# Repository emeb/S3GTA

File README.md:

# S3GTA
A Eurorack effects module based on the ESP32S3

## Abstract
This project builds on my previous ESP32S2 design:

https://github.com/emeb/ESP32S2_Audio

taking it further with a circular LCD, touch sensing and more CV inputs. It's
based on an ESP32S3 with 4MB flash and 2MB PSRAM in the package, as well as
dual CPU cores to potentially provide more DSP bandwidth.

### What's with the name?
I'm terrible at coming up with catchy names for my projects and this one is no
departure from that. It breaks down thus:
* S3 from the ESP32S3 processor
* G from the GC9A01 LCD
* T from the circular touch sensor
* A from audio I/O

## Hardware
The hardware consists of two PCBs - a front-panel board that provides the main
Eurorack user interface including a 240x240 circular LCD with a circular touch
sensor surrounding it and the MCU & audio codec, coupled with a back board that
includes the Eurorack power as well as audio and CV interfaces for the front-panel.

The front-panel PCB contains the following components:
* ESP32-S3FH4R2 MCU with 4MB flash and 2MB PSRAM integrated in the package
* WM8731 I2S audio codec
* 4 pad proportional circular touch sensor
* 4 CVs, stereo in/out and sync + button interfaces to back board.
* optional USB and Qwicc connectors

The back board has
* Standard Eurorack 16-pin shrouded power connector
* Four +/-5V CV inputs and associated analog signal conditioning
* Four offset pots for the CVs
* Two +/-7V Audio inputs and associated analog signal conditioning 
* Two +/-7V Audio outputs and associated analog drivers
* Tap tempo button
* Sync input jack

## Firmware
A demonstration firmware is included that exercises all of the capabilities of
the system, including the LCD, UI button, CV inputs and stereo audio I/O. It is
a basic multi-effects unit that supports a complement of audio DSP algorithms
that are easily extended by adding standardized modules to a data structure.
As provided here just three algorithms are available:
* Simple pass-thru with no processing
* Simple gain control
* Lowpass, Highpass and Bandpass filters
* Basic "clean delay" with crossfaded deglitching during delay changes.

Other algorithms have been tested including phasers, flangers, frequency shifters,
resampling delays and reverbs, but these are not publicly released at this time.

## Findings
The ESP32Ss is not bad for doing audio and the I2S driver in ESP-IDF V5.2.3 does
include good support for realtime audio processing. There are a few hiccups in
the way it works that are commented in the source code, but overall it does a
good job of supporting audio effects processing.

I found that in general the DSP on the ESP32S3 was usable, although not as
efficient as on ARM processors. Some algorithms showed significantly higher CPU
loading on the ESP32S3 than on ARM Cortex M7, even accounting for clock speed
differences. Studying the disassembly of the object code suggests that the full
DSP capability of the ESP32S3 Xtensa CPU ISA isn't being brought to bear by the
GCC compiler - for example the available multiply-accumulate instructions were
not used in cases where they may have reduced overall instruction counts.

## Future work
The UI is fairly primitive and doesn't make effective use of the circular touch
sensor. In the initial release there are only two "soft buttons" that employ
the touch sensor to select the current algorithm and this could be extended
to allow more soft buttons, deeper menuing and even continuously variable
adjustmets for things like on-board modulation.

The graphic elements on the circular LCD are also pretty tiny and hard to read
while also not taking full advantage of the available LCD area. It would be
interesting to "lean in" to the round nature of the display with more arcs
and circular UI elements. Fatter lines and larger fonts would help a lot too.
One option is to ditch the home-made graphics library I used here and try to
leverage LVGL which is available as an external module in ESP IDF - I did a
bit of research into this at the outset but went with my existing graphics
for ease of porting older code.

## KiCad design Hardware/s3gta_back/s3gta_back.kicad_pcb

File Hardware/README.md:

# S3GTA Hardware
This directory contains the Kicad designs for the front and back PCBs

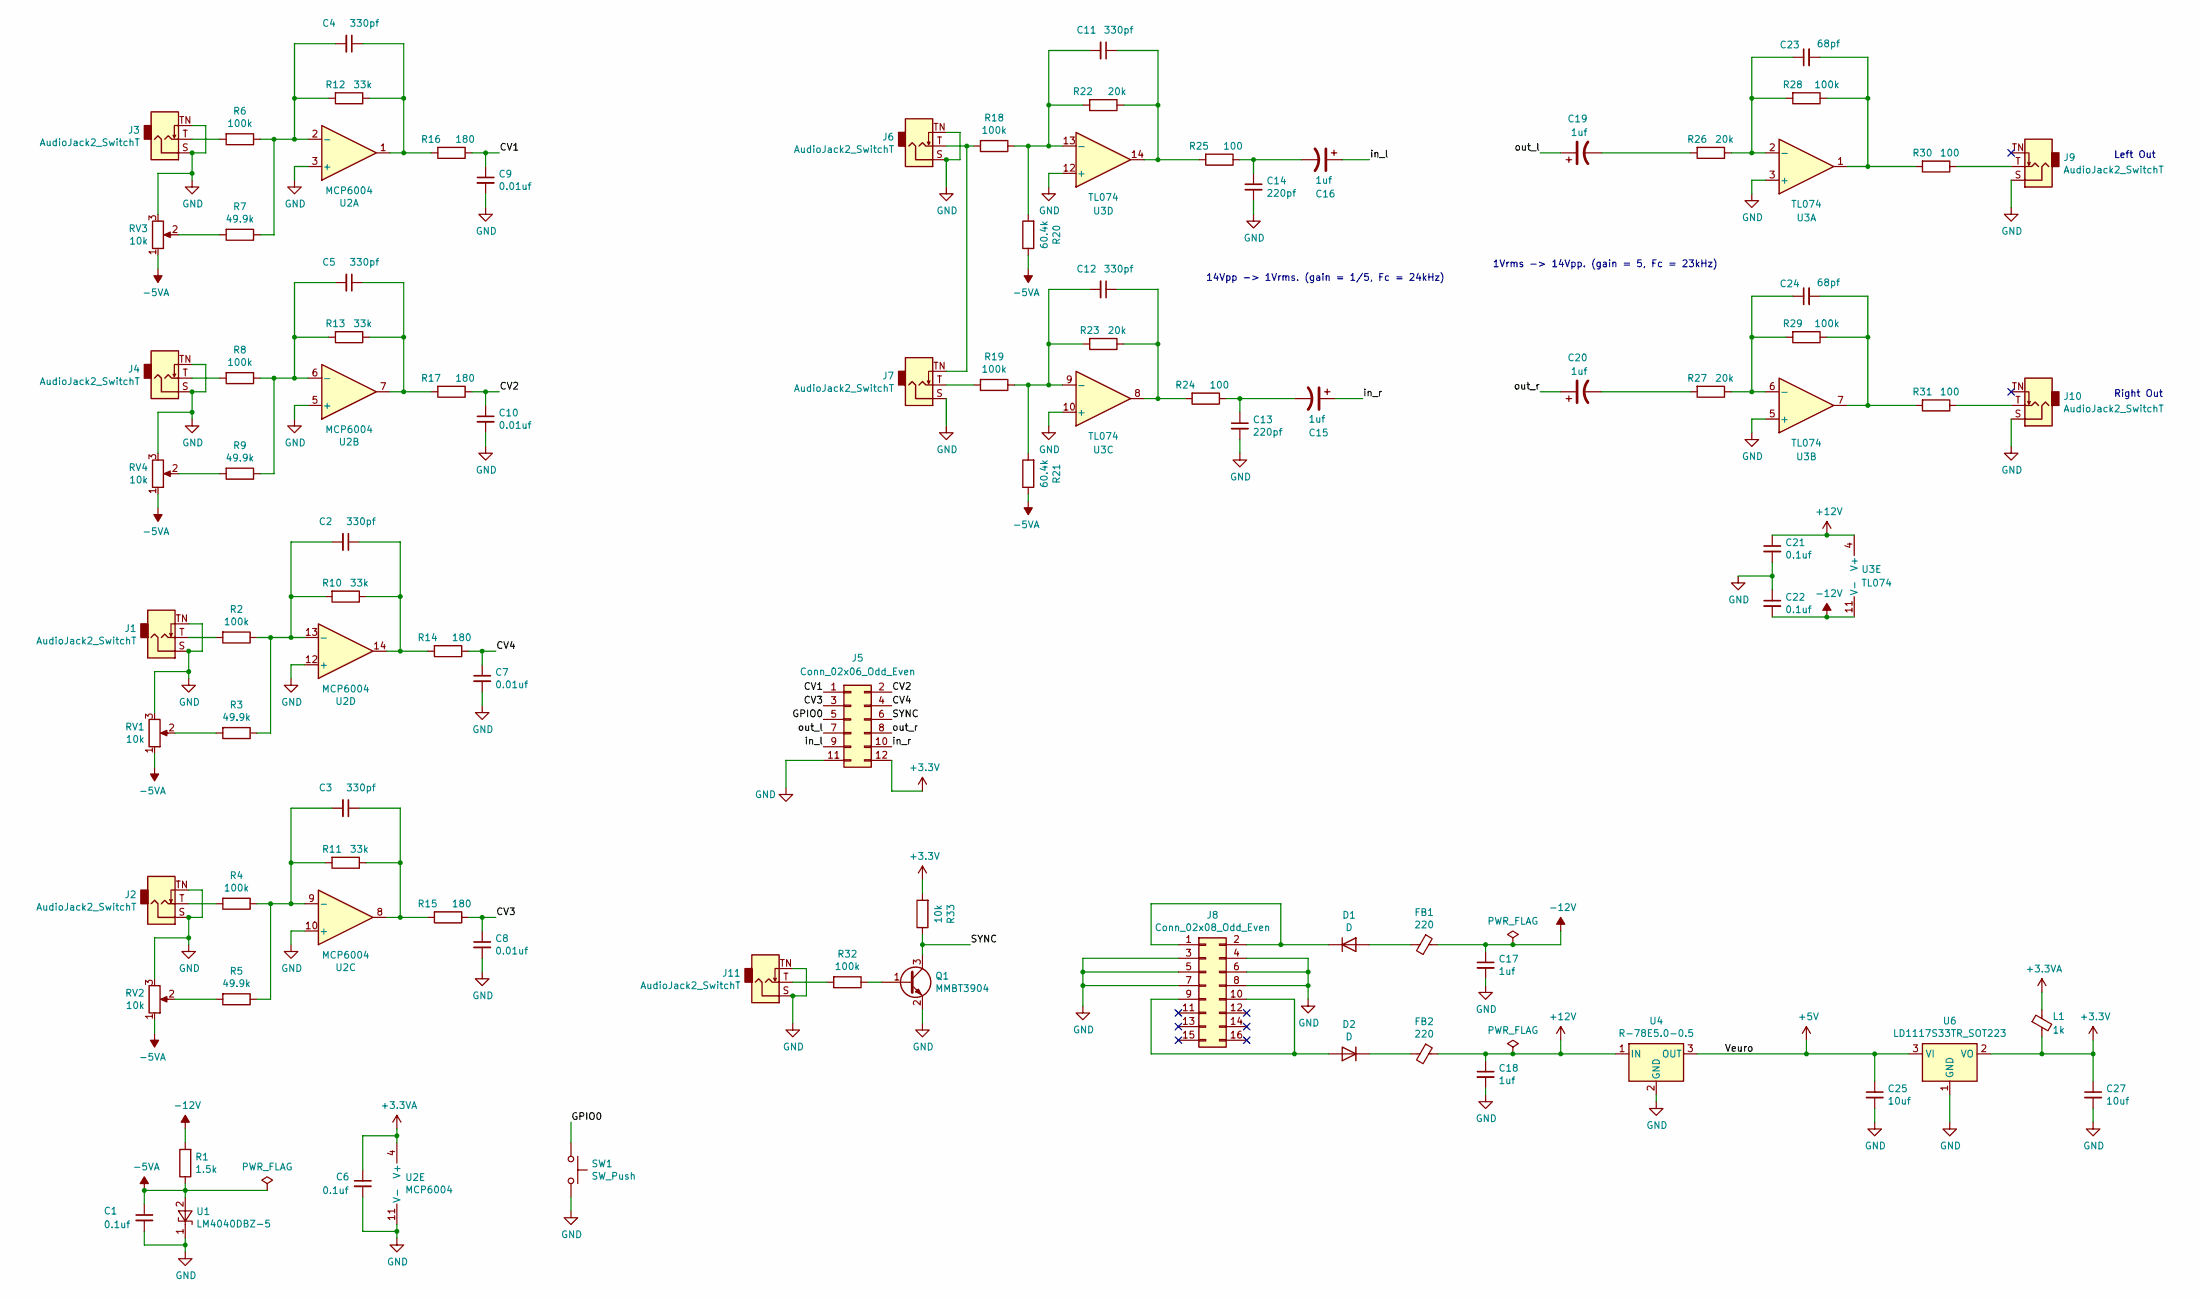
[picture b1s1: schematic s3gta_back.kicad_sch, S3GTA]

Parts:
C1, C6, C21, C22: 0.1uf; C_0603_1608Metric
C2, C3, C4, C5, C11, C12: 330pf; C_0603_1608Metric
C7, C8, C9, C10: 0.01uf; C_0603_1608Metric
C13, C14: 220pf; C_0603_1608Metric
C15, C16, C19, C20: 1uf; CP_Elec_4x5.3
C17, C18: 1uf; C_0603_1608Metric
C23, C24: 68pf; C_0603_1608Metric
C25, C27: 10uf; C_0805_2012Metric
D1, D2: D; D_SMA
FB1, FB2: 220; L_0805_2012Metric
J1, J2, J3, J4, J6, J7, J9, J10, J11: AudioJack2_SwitchT; Jack_3.5mm_QingPu_WQP-PJ398SM_Vertical_CircularHoles
J5: Conn_02x06_Odd_Even; PinSocket_2x06_P2.54mm_Vertical
J8: Conn_02x08_Odd_Even; con16_2X8_S4_TEC
L1: 1k; L_0603_1608Metric
Q1: MMBT3904; SOT-23
R1: 1.5k; R_0603_1608Metric
R2, R4, R6, R8, R18, R19, R28, R29, R32: 100k; R_0603_1608Metric
R3, R5, R7, R9: 49.9k; R_0603_1608Metric
R10, R11, R12, R13: 33k; R_0603_1608Metric
R14, R15, R16, R17: 180; R_0603_1608Metric
R20, R21: 60.4k; R_0603_1608Metric
R22, R23, R26, R27: 20k; R_0603_1608Metric
R24, R25, R30, R31: 100; R_0603_1608Metric
R33: 10k; R_0603_1608Metric
RV1, RV2, RV3, RV4: 10k; R0904N
SW1: SW_Push; SW_PUSH_6mm
U1: LM4040DBZ-5; SOT-23
U2: MCP6004; SOIC-14_3.9x8.7mm_P1.27mm
U3: TL074; SOIC-14_3.9x8.7mm_P1.27mm
U4: R-78E5.0-0.5; Converter_DCDC_RECOM_R-78E-0.5_THT
U6: LD1117S33TR_SOT223; SOT-223-3_TabPin2

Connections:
+3.3V: C27.1, J5.12, L1.2, R33.2, U6.2 (VO)
+3.3VA: C6.1, L1.1, U2.4 (V+)
+5V: C25.1, U4.3 (OUT), U6.3 (VI)
+12V: C18.1, C21.1, FB2.1, U3.4 (V+), U4.1 (IN)
-5VA: C1.1, R1.1, R20.1, R21.1, RV1.1, RV2.1, RV3.1, RV4.1, U1.2 (A)
-12V: C17.1, C22.2, FB1.1, R1.2, U3.11 (V-)
/CV1: C9.1, J5.1, R16.1
/CV2: C10.1, J5.2, R17.1
/CV3: C8.1, J5.3, R15.1
/CV4: C7.1, J5.4, R14.1
/GPIO0: J5.5, SW1.1
/SYNC: J5.6, Q1.3 (C), R33.1
/in_l: C16.1, J5.9
/in_r: C15.1, J5.10
/out_l: C19.1, J5.7
/out_r: C20.1, J5.8
GND: C1.2, C6.2, C7.2, C8.2, C9.2, C10.2, C13.2, C14.2, C17.2, C18.2, C21.2, C22.1, C25.2, C27.2, J1.S, J1.TN, J2.S, J2.TN, J3.S, J3.TN, J4.S, J4.TN, J5.11, J6.S, J6.TN, J7.S, J8.3, J8.4, J8.5, J8.6, J8.7, J8.8, J9.S, J10.S, J11.S, J11.TN, Q1.2 (E), RV1.3, RV2.3, RV3.3, RV4.3, SW1.2, U1.1 (K), U2.3 (+), U2.5 (+), U2.10 (+), U2.11 (V-), U2.12 (+), U3.3 (+), U3.5 (+), U3.10 (+), U3.12 (+), U4.2 (GND), U6.1 (GND)
unnamed: C2.1, R10.1, R14.2, U2.14
unnamed: C3.1, R11.1, R15.2, U2.8
unnamed: C4.1, R12.1, R16.2, U2.1
unnamed: C5.1, R13.1, R17.2, U2.7
unnamed: C11.1, R22.1, R25.2, U3.14
unnamed: C12.1, R23.1, R24.2, U3.8
unnamed: C13.1, C15.2, R24.1
unnamed: C14.1, C16.2, R25.1
unnamed: C19.2, R26.2
unnamed: C20.2, R27.2
unnamed: C23.2, R28.1, R30.2, U3.1
unnamed: C24.2, R29.1, R31.2, U3.7
unnamed: D1.2 (A), FB1.2
unnamed: D1.1 (K), J8.1, J8.2
unnamed: D2.2 (A), J8.9, J8.10
unnamed: D2.1 (K), FB2.2
unnamed: J1.T, R2.2
unnamed: J2.T, R4.2
unnamed: J3.T, R6.2
unnamed: J4.T, R8.2
unnamed: J6.T, J7.TN, R18.2
unnamed: J7.T, R19.2
unnamed: J9.T, R30.1
unnamed: J10.T, R31.1
unnamed: J11.T, R32.2
unnamed: Q1.1 (B), R32.1
unnamed: R3.2, RV1.2
unnamed: R5.2, RV2.2
unnamed: R7.2, RV3.2
unnamed: R9.2, RV4.2
unnamed: C4.2, R6.1, R7.1, R12.2, U2.2 (-)
unnamed: C5.2, R8.1, R9.1, R13.2, U2.6 (-)
unnamed: C3.2, R4.1, R5.1, R11.2, U2.9 (-)
unnamed: C2.2, R2.1, R3.1, R10.2, U2.13 (-)
unnamed: C23.1, R26.1, R28.2, U3.2 (-)
unnamed: C24.1, R27.1, R29.2, U3.6 (-)
unnamed: C12.2, R19.1, R21.2, R23.2, U3.9 (-)
unnamed: C11.2, R18.1, R20.2, R22.2, U3.13 (-)

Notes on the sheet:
1Vrms -> 14Vpp. (gain = 5, Fc = 23kHz)
14Vpp -> 1Vrms. (gain = 1/5, Fc = 24kHz)
Right Out
Left Out

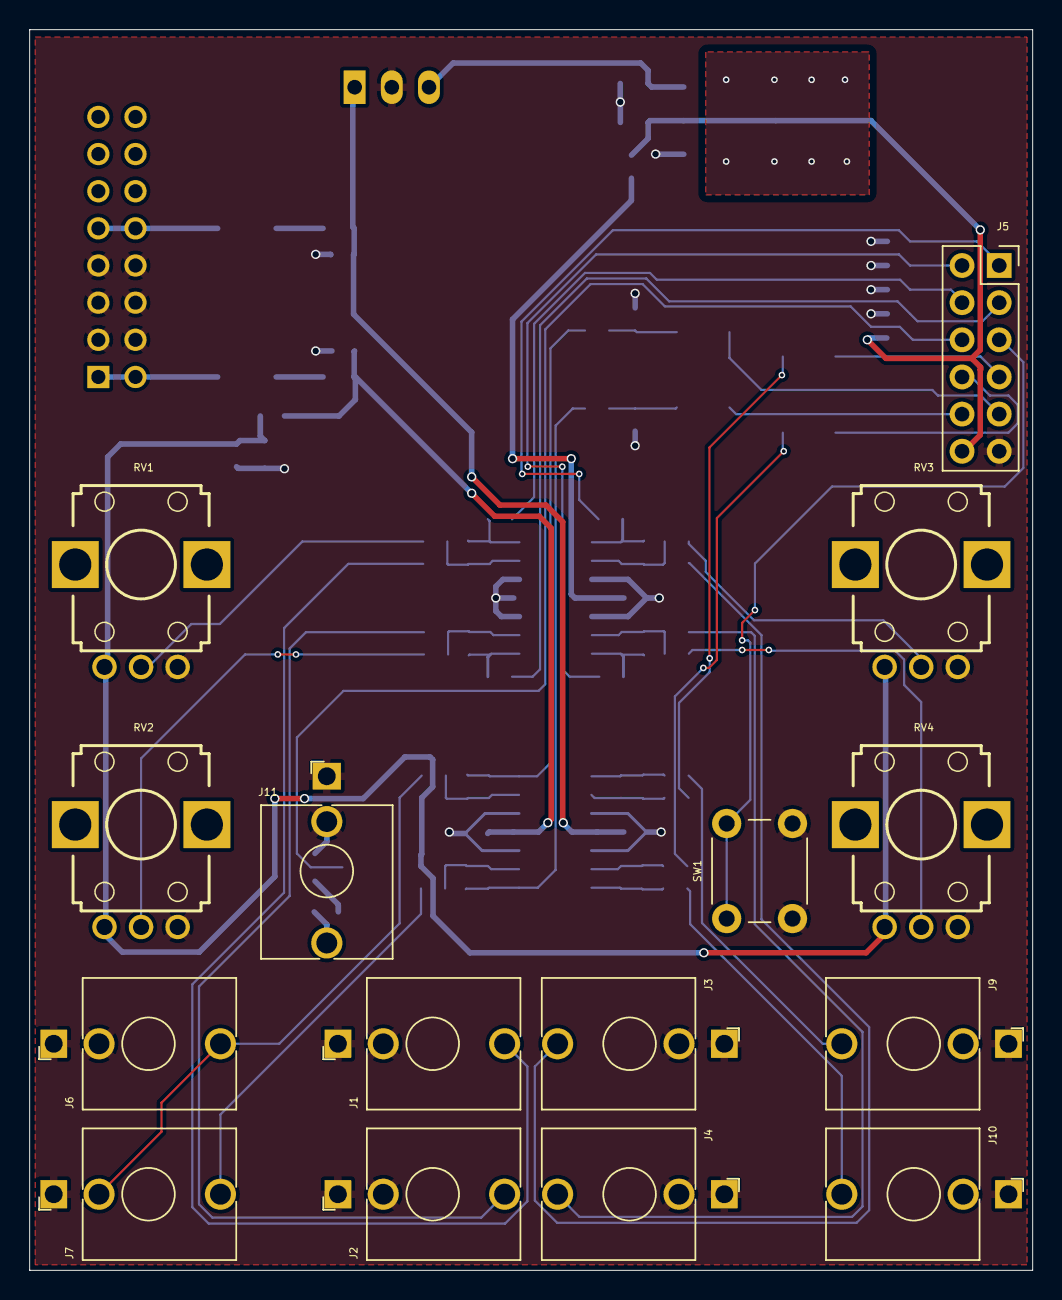
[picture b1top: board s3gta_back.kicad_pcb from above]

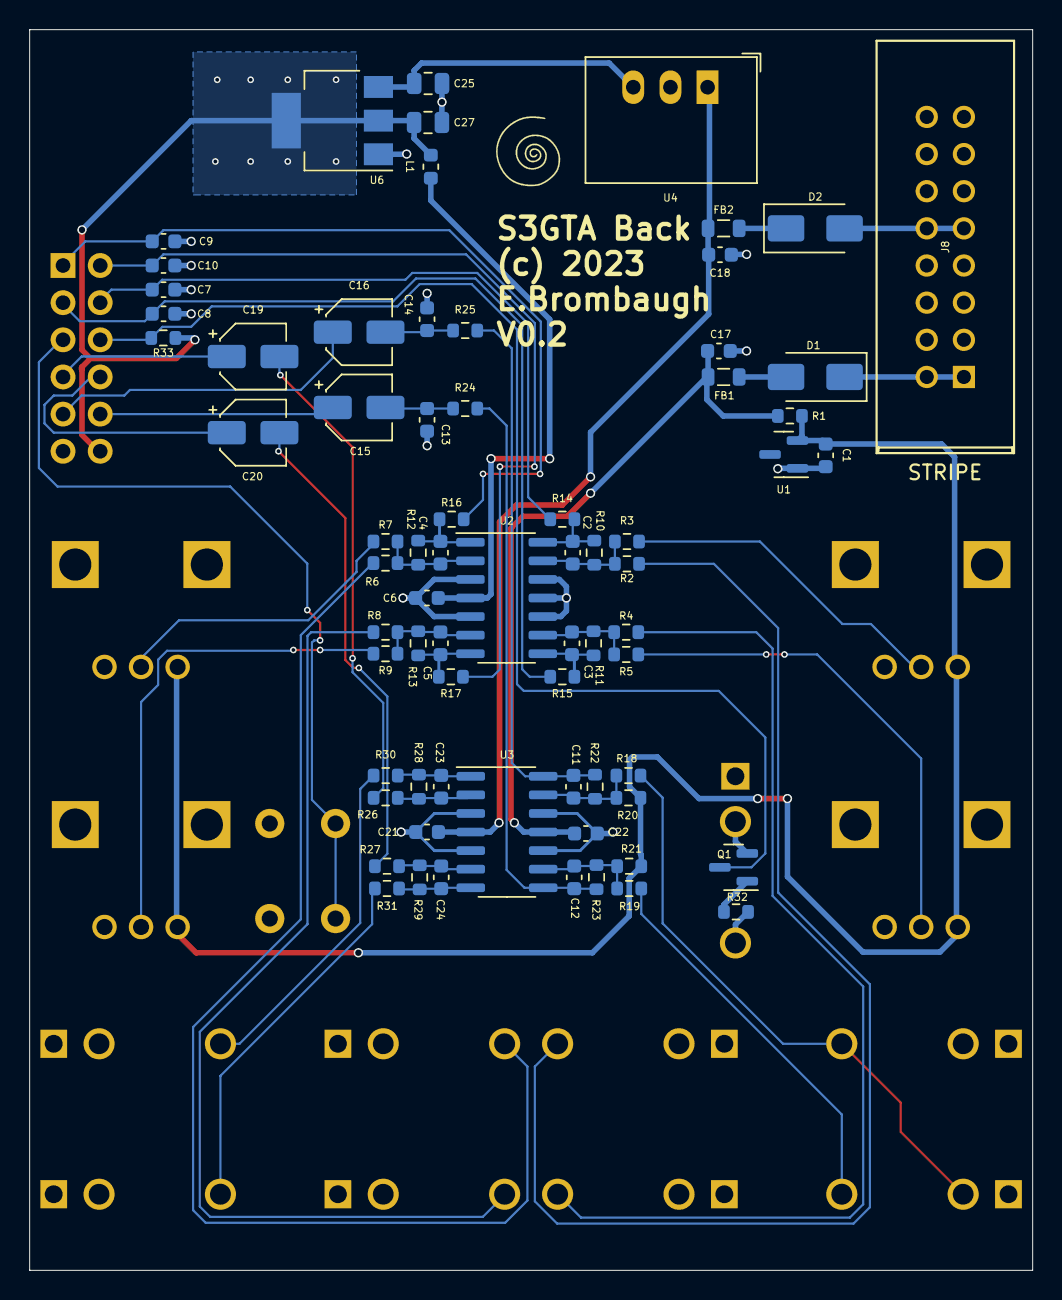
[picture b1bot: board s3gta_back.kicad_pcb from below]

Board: 2 copper layers, 68.6 x 84.8 mm, 87 parts (72 on the bottom side), 55 nets.

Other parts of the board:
Ref**: Val**; avatar_small

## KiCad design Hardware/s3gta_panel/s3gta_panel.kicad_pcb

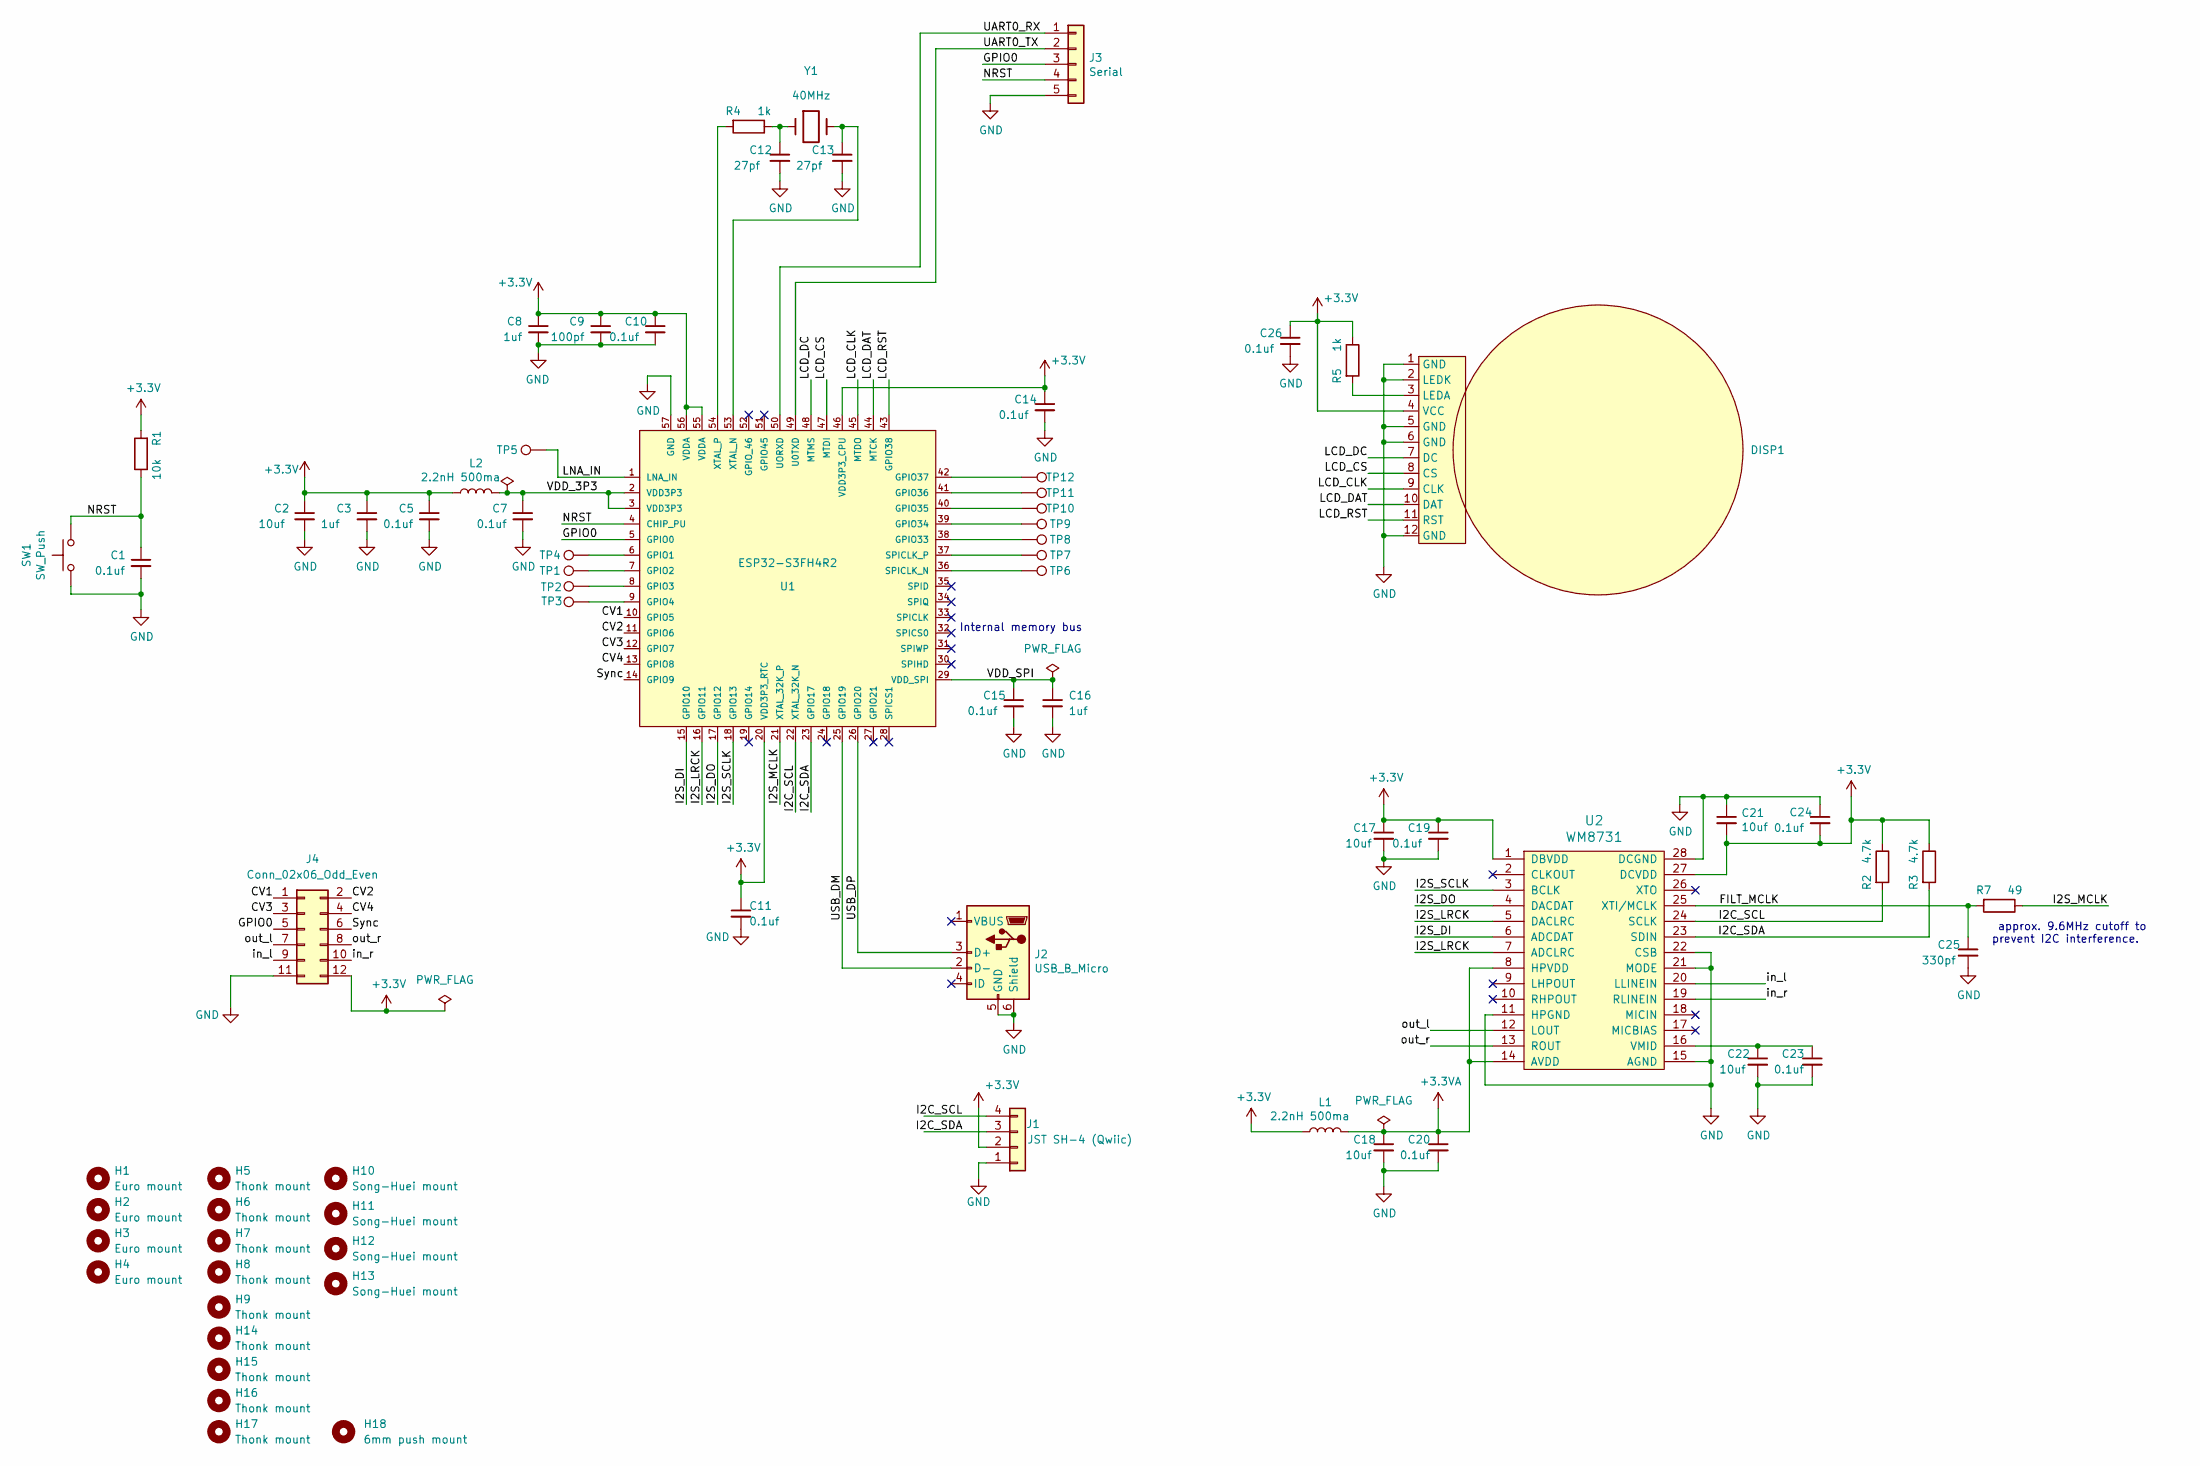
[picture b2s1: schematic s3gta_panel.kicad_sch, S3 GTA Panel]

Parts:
C1, C5, C7, C10, C11, C14, C15, C19, C20, C23, C24, C26: 0.1uf; C_0603_1608Metric
C2, C17, C18, C21, C22: 10uf; C_0805_2012Metric
C3, C8, C16: 1uf; C_0603_1608Metric
C9: 100pf; C_0603_1608Metric
C12, C13: 27pf; C_0603_1608Metric
C25: 330pf; C_0603_1608Metric
DISP1: Round_LCD_GC9A01
H1, H2, H3, H4: Euro mount; Mount_Hole_Euro_Rack
H5, H6, H7, H8, H9, H14, H15, H16, H17: Thonk mount; Mount_Hole_Thonk
H10, H11, H12, H13: Song-Huei mount; Mount_Hole_Song_Huei
H18: 6mm push mount; Mount_Hole_Toggle_Submini
J1: JST SH-4 (Qwiic); JST_SH_SM04B-SRSS-TB_04x1.00mm_Angled
J2: USB_B_Micro; USB_Micro-B_10103594-0001LF_actual_outline
J3: Serial; Harwin_M20-89005xx_1x05_P2.54mm_Horizontal
J4: Conn_02x06_Odd_Even; PinHeader_2x06_P2.54mm_Vertical_SMD
L1, L2: 2.2nH 500ma; C_0603_1608Metric
R1: 10k; R_0603_1608Metric
R2, R3: 4.7k; R_0603_1608Metric
R4, R5: 1k; R_0603_1608Metric
R7: 49; R_0603_1608Metric
SW1: SW_Push; SW_Push_1P1T_NO_CK_KMR2
TP1, TP2, TP3, TP4: TouchPad; quarter_touch
TP5, TP6, TP7, TP8, TP9, TP10, TP11, TP12: TouchPad; TestPoint_Pad_D0.5mm
U1: ESP32-S3FH4R2; ESP32-S3; mouser part number 356-ESP32-S2; digikey description RX TXRX MOD WIFI SURFACE MOUNT
U2: WM8731; SSOP-28_5.3x10.2mm_P0.65mm
Y1: 40MHz; Crystal_SMD_3225-4Pin_3.2x2.5mm

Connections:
+3.3V: C2.1, C3.1, C5.1, C8.1, C9.1, C10.1, C11.1, C14.1, C17.1, C19.1, C21.2, C24.2, C26.1, DISP1.4 (VCC), J1.2, J4.12, L1.1, L2.1, R1.2, R2.1, R3.1, R5.1, U1.20 (VDD3P3_RTC), U1.46 (VDD3P3_CPU), U1.55 (VDDA), U1.56 (VDDA), U2.1 (DBVDD), U2.27 (DCVDD)
+3.3VA: C18.1, C20.1, L1.2, U2.8 (HPVDD), U2.14 (AVDD)
/CV1: J4.1, U1.10 (GPIO5)
/CV2: J4.2, U1.11 (GPIO6)
/CV3: J4.3, U1.12 (GPIO7)
/CV4: J4.4, U1.13 (GPIO8)
/FILT_MCLK: C25.1, R7.2, U2.25 (XTI/MCLK)
/GPIO0: J3.3, J4.5, U1.5 (GPIO0)
/I2C_SCL: J1.4, R2.2, U1.22 (XTAL_32K_N), U2.24 (SCLK)
/I2C_SDA: J1.3, R3.2, U1.23 (GPIO17), U2.23 (SDIN)
/I2S_DI: U1.15 (GPIO10), U2.6 (ADCDAT)
/I2S_DO: U1.17 (GPIO12), U2.4 (DACDAT)
/I2S_LRCK: U1.16 (GPIO11), U2.5 (DACLRC), U2.7 (ADCLRC)
/I2S_MCLK: R7.1, U1.21 (XTAL_32K_P)
/I2S_SCLK: U1.18 (GPIO13), U2.3 (BCLK)
/LCD_CLK: DISP1.9 (CLK), U1.45 (MTDO)
/LCD_CS: DISP1.8 (CS), U1.47 (MTDI)
/LCD_DAT: DISP1.10 (DAT), U1.44 (MTCK)
/LCD_DC: DISP1.7 (DC), U1.48 (MTMS)
/LCD_RST: DISP1.11 (RST), U1.43 (GPIO38)
/LNA_IN: TP5.1, U1.1 (LNA_IN)
/NRST: C1.1, J3.4, R1.1, SW1.1, U1.4 (CHIP_PU)
/Sync: J4.6, U1.14 (GPIO9)
/UART0_RX: J3.1, U1.50 (UORXD)
/UART0_TX: J3.2, U1.49 (U0TXD)
/USB_DM: J2.2 (D-), U1.25 (GPIO19)
/USB_DP: J2.3 (D+), U1.26 (GPIO20)
/VDD_3P3: C7.1, L2.2, U1.2 (VDD3P3), U1.3 (VDD3P3)
/VDD_SPI: C15.1, C16.1, U1.29 (VDD_SPI)
/in_l: J4.9, U2.20 (LLINEIN)
/in_r: J4.10, U2.19 (RLINEIN)
/out_l: J4.7, U2.12 (LOUT)
/out_r: J4.8, U2.13 (ROUT)
GND: C1.2, C2.2, C3.2, C5.2, C7.2, C8.2, C9.2, C10.2, C11.2, C12.2, C13.2, C14.2, C15.2, C16.2, C17.2, C18.2, C19.2, C20.2, C21.1, C22.2, C23.2, C24.1, C25.2, C26.2, DISP1.1 (GND), DISP1.2 (LEDK), DISP1.5 (GND), DISP1.6 (GND), DISP1.12 (GND), J1.1, J2.5 (GND), J2.6 (Shield), J3.5, J4.11, SW1.2, U1.57 (GND), U2.11 (HPGND), U2.15 (AGND), U2.21 (MODE), U2.22 (CSB), U2.28 (DCGND)
unnamed: C12.1, R4.1, Y1.1
unnamed: DISP1.3 (LEDA), R5.2
unnamed: TP4.1, U1.6 (GPIO1)
unnamed: TP1.1, U1.7 (GPIO2)
unnamed: TP2.1, U1.8 (GPIO3)
unnamed: TP3.1, U1.9 (GPIO4)
unnamed: TP8.1, U1.38 (GPIO33)
unnamed: TP9.1, U1.39 (GPIO34)
unnamed: TP10.1, U1.40 (GPIO35)
unnamed: TP11.1, U1.41 (GPIO36)
unnamed: TP12.1, U1.42 (GPIO37)
unnamed: TP6.1, U1.36 (SPICLK_N)
unnamed: TP7.1, U1.37 (SPICLK_P)
unnamed: C13.1, U1.53 (XTAL_N), Y1.3
unnamed: R4.2, U1.54 (XTAL_P)
unnamed: C22.1, C23.1, U2.16 (VMID)

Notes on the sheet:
Internal memory bus
approx. 9.6MHz cutoff to prevent I2C interference.

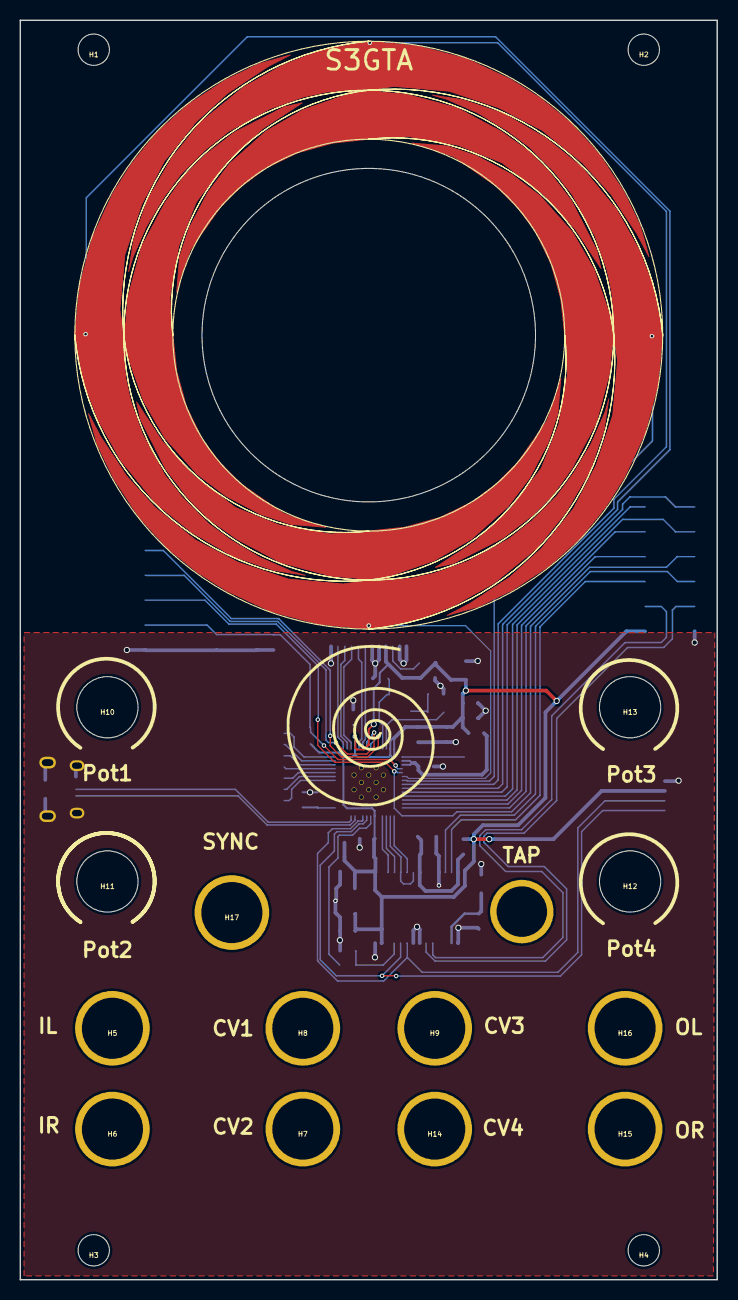
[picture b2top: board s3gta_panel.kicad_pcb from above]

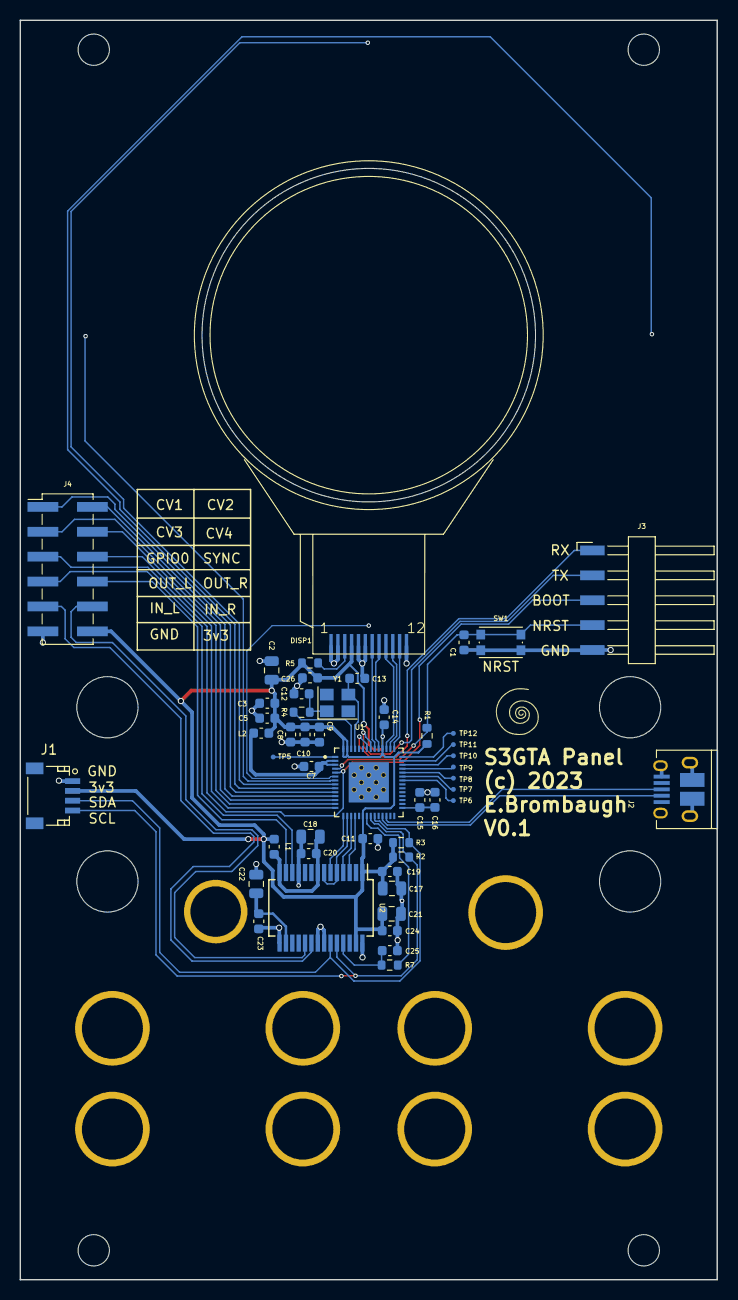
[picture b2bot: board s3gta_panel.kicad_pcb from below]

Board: 2 copper layers, 71.1 x 128.5 mm, 73 parts (50 on the bottom side), 50 nets.

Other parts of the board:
Ref**: Val**; avatar
Ref**#2: Val**; avatar_small

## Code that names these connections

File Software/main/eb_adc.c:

/*
 * eb_adc.c - my high-level ADC driver. Mimics background ADC operation.
 * 01-16-22 E. Brombaugh
 */
 
#include <stdio.h>
#include "main.h"
//#include "driver/adc.h"
#include "esp_adc/adc_oneshot.h"
#include "driver/gpio.h"
#include "esp_timer.h"
#include "hal/i2s_hal.h"
#include "hal/i2s_types.h"
#include <soc/sens_reg.h>
#include <soc/sens_struct.h>
#include <soc/spi_reg.h>
#include <soc/spi_struct.h>
#include "eb_adc.h"

static const char* TAG = "eb_adc";
static uint8_t adc_idx, adc_hyst_state, adc_param_idx;
//static int16_t adc_hyst_val;
int32_t adc_iir[ADC_NUMVALS];
volatile int16_t adc_val[ADC_NUMVALS], adc_param[ADC_NUMPARAMS];

#define GET_UNIT(x)			((x>>3) & 0x1)
#define TIMES				8

/*
 * channel mapping:
 * POT 1 - CV4 - GPIO8 - CHL7
 * POT 2 - CV3 - GPIO7 - CHL6
 * POT 3 - CV1 - GPIO5 - CHL4
 * POT 4 - CV2 - GPIO6 - CHL5
 */
const uint8_t adc_chls[ADC_NUMVALS] =
{
	ADC_CHANNEL_7,
	ADC_CHANNEL_6,
	ADC_CHANNEL_4,
	ADC_CHANNEL_5,	
};

/*
 * low-level: set channel, wait for ready & start conversion
 * cuts time from 45us to 15us
 */
void IRAM_ATTR my_adc1_get_raw_begin(uint8_t chl)
{
	SENS.sar_meas1_ctrl2.sar1_en_pad = (1 << chl);
	/* note that this reg is undocumented! */
	while (HAL_FORCE_READ_U32_REG_FIELD(SENS.sar_slave_addr1, meas_status) != 0) {}
	SENS.sar_meas1_ctrl2.meas1_start_sar = 0;
	SENS.sar_meas1_ctrl2.meas1_start_sar = 1;
}

/*
 * low-level: wait for eoc & fetch result
 */
int16_t IRAM_ATTR my_adc1_get_raw_end(void)
{
    while (SENS.sar_meas1_ctrl2.meas1_done_sar == 0);
    return 4095-HAL_FORCE_READ_U32_REG_FIELD(SENS.sar_meas1_ctrl2, meas1_data_sar);
}

/*
 * IIR filter for 12-bit ADC values 
 */
#define IIR_COEF 4
inline int16_t adc_IIR_filter(int32_t *filt_state, int16_t in)
{
	*filt_state += ((in<<IIR_COEF) - *filt_state )>>IIR_COEF;
	return *filt_state >> (IIR_COEF);
}

/*
 * ADC timer callback
 */
void IRAM_ATTR adc_timer_callback(void *arg)
{
	/* set ISR active flag */
	//gpio_set_level(DIAG_1, 1);
	
	/* don't wait for conversion - get previous result */
	adc_val[adc_idx] = adc_IIR_filter(&adc_iir[adc_idx], my_adc1_get_raw_end());

#if 0
	/* handle hysteresis */
	if(adc_idx<(ADC_NUMVALS-1))
	{
		/* update parameter */
		switch(adc_hyst_state)
		{
			case 0:	/* reset */
				adc_hyst_val = adc_val[1];
				adc_hyst_state = 1;
				break;
			
			case 1: /* locked & waiting for unlock */
				if(abs(adc_val[1]-adc_hyst_val) > 200)
					adc_hyst_state = 2;
				break;
			
			case 2:	/* tracking */
				adc_param[adc_param_idx] = adc_val[1];
				break;
		}
	}
#else
	/* just pass thru to params */
	adc_param[adc_idx] = adc_val[adc_idx];
#endif

	/* advance channel */
	adc_idx = (adc_idx + 1)%ADC_NUMVALS;
	
	/* start next conversion */
	my_adc1_get_raw_begin(adc_chls[adc_idx]);
	
	/* clear ISR active flag */
	//gpio_set_level(DIAG_1, 0);
}

esp_err_t eb_adc_init(void)
{
	uint8_t i;
	esp_timer_handle_t timer_handle;
	
	/* setup state */
	adc_idx = 0;
	adc_hyst_state = 0;
	adc_param_idx = 0;
	
	/* single conversions w/ timer */
#if 0
	/* OLD API is deprecated */
    ESP_LOGI(TAG, "PIO mode w/ deprecated driver");
	adc1_config_width(ADC_WIDTH_BIT_12);
	adc1_config_channel_atten(CV0, ADC_ATTEN_DB_6);
	adc1_config_channel_atten(CV1, ADC_ATTEN_DB_6);
	adc1_get_raw(CV0);
#else
	/* New one-shot API */
    ESP_LOGI(TAG, "PIO mode w/ new one-shot driver");
	/* init ADC1 */
	adc_oneshot_unit_handle_t adc1_handle;
	adc_oneshot_unit_init_cfg_t init_config1 = {
		.unit_id = ADC_UNIT_1,
		.ulp_mode = ADC_ULP_MODE_DISABLE,
	};
	ESP_ERROR_CHECK(adc_oneshot_new_unit(&init_config1, &adc1_handle));
	
	/* set up channels: GPIO 5-8 are ADC1 chls 4-7 */
	adc_oneshot_chan_cfg_t config = {
		.bitwidth = SOC_ADC_RTC_MAX_BITWIDTH,	// defaults to 12 bit on S3
		.atten = ADC_ATTEN_DB_6,
	};
	for(i=0;i<ADC_NUMVALS;i++)
		ESP_ERROR_CHECK(adc_oneshot_config_channel(adc1_handle, adc_chls[i], &config));

	/* read a channel to start ADC */
	int dummy;
	ESP_ERROR_CHECK(adc_oneshot_read(adc1_handle, adc_chls[0], &dummy));
#endif
	
	/* Timer for controlling ADC sampling intervals */
	esp_timer_create_args_t timer_args = {
		.callback = adc_timer_callback,
		.arg = NULL,
		.name = "adc_timer",
		.skip_unhandled_events = true
	};
	esp_timer_create(&timer_args, &timer_handle);
	esp_timer_start_periodic(timer_handle, 1000);
	
	return ESP_OK;
}

/*
 * set adc[1] parameter destination
 */
void eb_adc_setactparam(uint8_t idx)
{
	if(idx>=ADC_NUMPARAMS)
		return;
	
	if(idx != adc_param_idx)
	{
		/* this has to be atomic */
		taskDISABLE_INTERRUPTS();
		adc_param_idx = idx;
		adc_hyst_state = 0;
		taskENABLE_INTERRUPTS();
	}
}

/*
 * set adc[1] parameter value
 */
void eb_adc_setparamval(uint8_t idx, int16_t val)
{
	if(idx>=ADC_NUMPARAMS)
		return;
	
	adc_param[idx] = val;
}

/*
 * force adc[1] active parameter hysteresis to track live value
 */
void eb_adc_forceactparam(void)
{
	adc_hyst_state = 2;
}

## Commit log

2025-01-01 Initial release
2025-01-01 Added image

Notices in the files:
Hardware/s3gta_back/s3gta_back.kicad_pcb:
(c) 2023
